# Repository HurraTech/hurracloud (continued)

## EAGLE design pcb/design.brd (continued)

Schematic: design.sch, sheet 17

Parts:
C16, C18, C22, C23, C24, C26, C27, C28, C29, C31, C32, C33, C294, C295, C296, C303, C314: GRM033R60J104KE19D; 0201
C17, C25, C34: CGB3B1X5R1A475K055AC; 0603
C19: 22uF; 0805
C20, C21: GRM0335C1H220JA01D; 0201
IC7: EP5368QI; EP-3X3MMQFN16
R3, R65, R69: RC0201JR-070RL; 0201
R9, R67: DNP; 0201
R10, R11: ERJ-1GEJ204C; 0201
R13: 1M0; 0201
R14, R15: RC0201FR-0710KL; 0201
R16: ERJ-1GEF1202C; 0201
R66: ERJ-1GNF10R0C; 0201
U15: USB5744/2G; VQFN56
Y2: ABM7-25.000MHZ-D2Y-T; CS10

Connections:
14.3.3V_VCC_3.3: C16.1, C17.1, C22.1, C23.1, C24.1, C25.1, IC7.10 (VS2), IC7.12 (VS0), IC7.13 (ENABLE), IC7.14 (VIN), R9.2, R14.2, R15.2, R67.2, U15.16 (VDD33), U15.31 (VDD33), U15.44 (VDD33), U15.55 (VDD33); also elsewhere on the board
16.USBH1_D_N: U15.46 (USB2UP_DM); also elsewhere on the board
16.USBH1_D_P: U15.45 (USB2UP_DP); also elsewhere on the board
16.USBH1_SSRX_N: C295.1; also elsewhere on the board
16.USBH1_SSRX_P: C296.1; also elsewhere on the board
16.USBH1_SSTX_N: C303.1; also elsewhere on the board
16.USBH1_SSTX_P: C294.1; also elsewhere on the board
19.USBH1_DRV_VBUS: R65.2; also elsewhere on the board
19.USBH1_D_N: U15.2 (USB2DN_DM1); also elsewhere on the board
19.USBH1_D_P: U15.1 (USB2DN_DP1); also elsewhere on the board
19.USBH1_NOC: R65.1, U15.36 (PRT_CTL1); also elsewhere on the board
19.USBH1_SSRX_N: U15.7 (USB3DN_RXDM1); also elsewhere on the board
19.USBH1_SSRX_P: U15.6 (USB3DN_RXDP1); also elsewhere on the board
19.USBH1_SSTX_N: U15.4 (USB3DN_TXDM1); also elsewhere on the board
19.USBH1_SSTX_P: U15.3 (USB3DN_TXDP1); also elsewhere on the board
19.USBH2_DRV_VBUS: R69.2; also elsewhere on the board
19.USBH2_D_N: U15.9 (USB2DN_DM2); also elsewhere on the board
19.USBH2_D_P: U15.8 (USB2DN_DP2); also elsewhere on the board
19.USBH2_NOC: R69.1, U15.35 (PRT_CTL2); also elsewhere on the board
19.USBH2_SSRX_N: U15.14 (USB3DN_RXDM2); also elsewhere on the board
19.USBH2_SSRX_P: U15.13 (USB3DN_RXDP2); also elsewhere on the board
19.USBH2_SSTX_N: U15.11 (USB3DN_TXDM2); also elsewhere on the board
19.USBH2_SSTX_P: U15.10 (USB3DN_TXDP2); also elsewhere on the board
19.USBH3_DRV_VBUS: R3.2; also elsewhere on the board
19.USBH3_D_N: U15.18 (USB2DN_DM3); also elsewhere on the board
19.USBH3_D_P: U15.17 (USB2DN_DP3); also elsewhere on the board
19.USBH3_NOC: R3.1, U15.34 (PRT_CTL3); also elsewhere on the board
19.USBH3_SSRX_N: U15.23 (USB3DN_RXDM3); also elsewhere on the board
19.USBH3_SSRX_P: U15.22 (USB3DN_RXDP3); also elsewhere on the board
19.USBH3_SSTX_N: U15.20 (USB3DN_TXDM3); also elsewhere on the board
19.USBH3_SSTX_P: U15.19 (USB3DN_TXDP3); also elsewhere on the board
CAP_RXD_N$19: C295.2, U15.48 (USB3UP_TXDM)
CAP_RXD_P$19: C296.2, U15.47 (USB3UP_TXDP)
CAP_TXD_N$19: C303.2, U15.51 (USB3UP_RXDM)
CAP_TXD_P$19: C294.2, U15.50 (USB3UP_RXDP)
CFG_BC_EN$19: R11.2, R67.1, U15.40 (SPI_DI)
CFG_NON_REM$19: R9.1, R10.2, U15.41 (SPI_CE_N)
GND: C16.2, C17.2, C18.2, C19.2, C20.2, C21.2, C22.2, C23.2, C24.2, C25.2, C26.2, C27.2, C28.2, C29.2, C31.2, C32.2, C33.2, C34.2, C314.2, IC7.2 (PGND), IC7.6 (AGND), IC7.11 (VS1), R10.1, R11.1, R16.1, U15.52 (ATEST), U15.P$1 (VSS), U15.P$2 (VSS), U15.P$3 (VSS), U15.P$4 (VSS), U15.P$5 (VSS), U15.P$6 (VSS), U15.P$7 (VSS), U15.P$8 (VSS), U15.P$9 (VSS), U15.P$10 (VSS), U15.P$11 (VSS), U15.P$12 (VSS), U15.P$13 (VSS), U15.P$14 (VSS), U15.P$15 (VSS), U15.P$16 (VSS), U15.P$17 (VSS), U15.P$18 (VSS), U15.P$19 (VSS), U15.P$20 (VSS), U15.P$21 (VSS), U15.P$22 (VSS), U15.P$23 (VSS), U15.P$24 (VSS), U15.P$25 (VSS); also elsewhere on the board
RBIAS$19: R16.2, U15.56 (RBIAS)
RESET_N$19: R14.1, U15.42 (RESET_N)
USBH4_PCTL$19: U15.32 (PRT_CTL4)
VBUS_DET$19: R15.1, U15.37 (VBUS_DET)
VCC_1.2$19: C18.1, C19.1, C26.1, C27.1, C28.1, C29.1, C31.1, C32.1, C33.1, C34.1, C314.1, IC7.5 (VSENSE), IC7.7 (VOUT), IC7.8 (VOUT), U15.5 (VDD12), U15.12 (VDD12), U15.15 (VDD12), U15.21 (VDD12), U15.28 (VDD12), U15.33 (VDD12), U15.43 (VDD12), U15.49 (VDD12)
XTALIN$19: C21.1, R13.2, U15.54 (XTALIN), Y2.2
XTALOUT2$19: C20.1, R66.1, Y2.1
XTALOUT$19: R13.1, R66.2, U15.53 (XTALOUT)

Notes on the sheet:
4-Port USB 3.0 Hub

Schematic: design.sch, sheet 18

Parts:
C3: C1608X5R1A106M080AC; 0603
C7, C306: GRM31CR60J227ME11L; 1206
C8, C9, C10, C11, C304: GRM033R60J104KE19D; 0201
C305: GRM033R61C103KA12D; 0201
FB4, FB15, FB16, FB17: BLM15PX121SN1D; 0402
J6: GSB311231HR; USB3-A-H-DUAL
L4, L5, L6, L16, L17, L18: DLP11SN900HL2L; 0504-DLP11S
U2, U5, U6, U7, U20, U21: TPD4E02B04DQAR; UFDFN-10
U24: TPS2066CDGNR; MSOP8-PAD

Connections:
19.USBH1_DRV_VBUS: U24.3 (EN1); also elsewhere on the board
19.USBH1_D_N: L18.2; also elsewhere on the board
19.USBH1_D_P: L18.3; also elsewhere on the board
19.USBH1_GND_DRAIN: J6.7 (GND_DRAIN1), U7.2, U7.9 (P2)
19.USBH1_NOC: U24.8 (NOC1); also elsewhere on the board
19.USBH1_SSRX_N: L16.3; also elsewhere on the board
19.USBH1_SSRX_P: L16.2; also elsewhere on the board
19.USBH1_SSTX_N: C9.1; also elsewhere on the board
19.USBH1_SSTX_P: C8.1; also elsewhere on the board
19.USBH1_VBUS: FB4.2, U24.7 (OUT1)
19.USBH2_DRV_VBUS: U24.4 (EN2); also elsewhere on the board
19.USBH2_D_N: L4.2; also elsewhere on the board
19.USBH2_D_P: L4.3; also elsewhere on the board
19.USBH2_GND_DRAIN: J6.16 (GND_DRAIN2), U2.4 (P3), U2.7 (P3)
19.USBH2_NOC: U24.5 (NOC2); also elsewhere on the board
19.USBH2_SSRX_N: L5.3; also elsewhere on the board
19.USBH2_SSRX_P: L5.2; also elsewhere on the board
19.USBH2_SSTX_N: C11.1; also elsewhere on the board
19.USBH2_SSTX_P: C10.1; also elsewhere on the board
19.USBH2_VBUS: FB17.2, U24.6 (OUT2)
24.5.0V_VCC_5.0: C304.1, FB16.1; also elsewhere on the board
A_GNDF$20: C305.1, FB15.2, J6.4 (GND1), J6.13 (GND2), U5.1, U5.10 (P1), U21.1, U21.10 (P1)
A_USB_D_N$20: J6.2 (D1-), L18.1, U7.1, U7.10 (P1)
A_USB_D_P$20: J6.3 (D1+), L18.4, U7.5 (P4), U7.6 (P4)
A_VBUS_$20: C306.1, FB4.1, J6.1 (VBUS1), U6.1, U6.10 (P1)
B_USB_D_N$20: J6.11 (D2-), L4.1, U2.5 (P4), U2.6 (P4)
B_USB_D_P$20: J6.12 (D2+), L4.4, U2.1, U2.10 (P1)
B_VBUS_$20: C7.1, FB17.1, J6.10 (VBUS2), U20.5 (P4), U20.6 (P4)
CAP_A_TX_N$20: C9.2, L17.3
CAP_A_TX_P$20: C8.2, L17.2
CAP_B_TX_N$20: C11.2, L6.3
CAP_B_TX_P$20: C10.2, L6.2
COMMON_SHIELD: J6.S1 (SH1), J6.S2 (SH2), J6.S3 (SH3), J6.S4 (SH4), U2.3 (SHIELD), U2.8 (SHIELD), U5.3 (SHIELD), U5.8 (SHIELD), U6.3 (SHIELD), U6.8 (SHIELD), U7.3 (SHIELD), U7.8 (SHIELD), U20.3 (SHIELD), U20.8 (SHIELD), U21.3 (SHIELD), U21.8 (SHIELD); also elsewhere on the board
GND: C3.2, C7.2, C304.2, C305.2, C306.2, FB15.1, U24.1 (GND), U24.TP (GND); also elsewhere on the board
SSRX1_N$20: J6.5 (SSRX1-), L16.4, U5.4 (P3), U5.7 (P3)
SSRX1_P$20: J6.6 (SSRX1+), L16.1, U5.5 (P4), U5.6 (P4)
SSRX2_N$20: J6.14 (SSRX2-), L5.4, U21.4 (P3), U21.7 (P3)
SSRX2_P$20: J6.15 (SSRX2+), L5.1, U21.5 (P4), U21.6 (P4)
SSTX1_N$20: J6.8 (SSTX1-), L17.4, U6.5 (P4), U6.6 (P4)
SSTX1_P$20: J6.9 (SSTX1+), L17.1, U6.4 (P3), U6.7 (P3)
SSTX2_N$20: J6.17 (SSTX2-), L6.4, U20.1, U20.10 (P1)
SSTX2_P$20: J6.18 (SSTX2+), L6.1, U20.2, U20.9 (P2)
VBUSF$20: C3.1, FB16.2, U24.2 (IN)

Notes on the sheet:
USB 3.0 Stacking Dual

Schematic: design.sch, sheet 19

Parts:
J7: 70553-0002; 1X03_90_TH_SHROUD

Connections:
21.5.5-16V_VCC_BATT: J7.3; also elsewhere on the board
FRAME$21: J7.1
GND: J7.2; also elsewhere on the board

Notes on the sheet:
Molex 70553 3-Pin Header (Power Provides)

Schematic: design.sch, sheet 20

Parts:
C308, C309, C311, C312: GRM033R60J104KE19D; 0201
C310: GRM31CR60J227ME11L; 1206
D16: PS04LTVA1; D0402
FB18, FB19, FB20: BLM15PX121SN1D; 0402
IC9: SN74LV1T126DCKR; SC70-5
IC10: TPS2065CDGNR; MSOP8-PAD
J8: 10117836-002LF; USB3-A-H-VERT
L19, L20, L21: DLP11SN900HL2L; 0504-DLP11S
U22, U23: TPD4E02B04DQAR; UFDFN-10

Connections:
14.3.3V_VCC_3.3: C308.1, IC9.1 (OE), IC9.5 (VCC); also elsewhere on the board
16.USBH2_DRV_VBUS: IC9.2 (I); also elsewhere on the board
16.USBH2_D_N: L19.2; also elsewhere on the board
16.USBH2_D_P: L19.3; also elsewhere on the board
16.USBH2_GND_DRAIN: D16.P2, FB20.2, J8.DRAIN (GND_DRAIN), U23.4 (P3), U23.7 (P3)
16.USBH2_NOC: IC10.5 (NOC); also elsewhere on the board
16.USBH2_SSRX_N: L20.3; also elsewhere on the board
16.USBH2_SSRX_P: L20.2; also elsewhere on the board
16.USBH2_SSTX_N: C311.1; also elsewhere on the board
16.USBH2_SSTX_P: C312.1; also elsewhere on the board
16.USBH2_VBUS: FB18.1, IC10.6 (OUT), IC10.7 (OUT), IC10.8 (OUT)
24.5.0V_VCC_5.0: C309.1, IC10.2 (IN), IC10.3 (IN); also elsewhere on the board
COMMON_SHIELD: D16.P1, J8.SH1, J8.SH2, U22.3 (SHIELD), U22.8 (SHIELD), U23.3 (SHIELD), U23.8 (SHIELD); also elsewhere on the board
GND: C308.2, C309.2, C310.2, FB19.1, FB20.1, IC9.3 (GND), IC10.1 (GND), IC10.TP (GND); also elsewhere on the board
USBH_CPEN_3V$22: IC9.4 (O), IC10.4 (EN)
USBH_D_N$22: J8.D-, L19.1, U22.1, U22.10 (P1)
USBH_D_P$22: J8.D+, L19.4, U23.5 (P4), U23.6 (P4)
USBH_GND$22: FB19.2, J8.GND
USBH_VBUSF$22: C310.1, FB18.2, J8.VBUS, U22.2, U22.9 (P2)
USB_CAP_SSTX_N$22: C311.2, L21.3
USB_CAP_SSTX_P$22: C312.2, L21.2
USB_SSRX_N$22: J8.SSRX-, L20.4, U23.1, U23.10 (P1)
USB_SSRX_P$22: J8.SSRX+, L20.1, U23.2, U23.9 (P2)
USB_SSTX_N$22: J8.SSTX-, L21.4, U22.4 (P3), U22.7 (P3)
USB_SSTX_P$22: J8.SSTX+, L21.1, U22.5 (P4), U22.6 (P4)

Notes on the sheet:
USB 3.0 HOST (Vertical)

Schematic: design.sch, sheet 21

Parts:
C2: GRM31CR60J227ME11L; 1206
C4, C5, C6, C318: GRM033R60J104KE19D; 0201
D17: PS04LTVA1; D0402
FB1, FB2, FB3: BLM15PX121SN1D; 0402
IC1: TPS2065CDGNR; MSOP8-PAD
IC2: SN74LV1T126DCKR; SC70-5
J1: 10117836-002LF; USB3-A-H-VERT
L1, L3, L22: DLP11SN900HL2L; 0504-DLP11S
U3, U4: TPD4E02B04DQAR; UFDFN-10

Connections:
14.3.3V_VCC_3.3: C4.1, IC2.1 (OE), IC2.5 (VCC); also elsewhere on the board
19.USBH3_DRV_VBUS: IC2.2 (I); also elsewhere on the board
19.USBH3_D_N: L1.2; also elsewhere on the board
19.USBH3_D_P: L1.3; also elsewhere on the board
19.USBH3_GND_DRAIN: D17.P2, FB3.2, J1.DRAIN (GND_DRAIN), U4.4 (P3), U4.7 (P3)
19.USBH3_NOC: IC1.5 (NOC); also elsewhere on the board
19.USBH3_SSRX_N: L22.3; also elsewhere on the board
19.USBH3_SSRX_P: L22.2; also elsewhere on the board
19.USBH3_SSTX_N: C5.1; also elsewhere on the board
19.USBH3_SSTX_P: C6.1; also elsewhere on the board
19.USBH3_VBUS: FB1.1, IC1.6 (OUT), IC1.7 (OUT), IC1.8 (OUT)
24.5.0V_VCC_5.0: C318.1, IC1.2 (IN), IC1.3 (IN); also elsewhere on the board
COMMON_SHIELD: D17.P1, J1.SH1, J1.SH2, U3.3 (SHIELD), U3.8 (SHIELD), U4.3 (SHIELD), U4.8 (SHIELD); also elsewhere on the board
GND: C2.2, C4.2, C318.2, FB2.1, FB3.1, IC1.1 (GND), IC1.TP (GND), IC2.3 (GND); also elsewhere on the board
USBH_CPEN_3V$23: IC1.4 (EN), IC2.4 (O)
USBH_D_N$23: J1.D-, L1.1, U3.1, U3.10 (P1)
USBH_D_P$23: J1.D+, L1.4, U4.5 (P4), U4.6 (P4)
USBH_GND$23: FB2.2, J1.GND
USBH_VBUSF$23: C2.1, FB1.2, J1.VBUS, U3.2, U3.9 (P2)
USB_CAP_SSTX_N$23: C5.2, L3.3
USB_CAP_SSTX_P$23: C6.2, L3.2
USB_SSRX_N$23: J1.SSRX-, L22.4, U4.1, U4.10 (P1)
USB_SSRX_P$23: J1.SSRX+, L22.1, U4.2, U4.9 (P2)
USB_SSTX_N$23: J1.SSTX-, L3.4, U3.4 (P3), U3.7 (P3)
USB_SSTX_P$23: J1.SSTX+, L3.1, U3.5 (P4), U3.6 (P4)

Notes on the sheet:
USB 3.0 HOST (Vertical)

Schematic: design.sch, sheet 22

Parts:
C13: CL31A106KBHNNNE; 1206
C30: C0603C103K5RACTU; 0603
C52, C78: GRM033R61C103KA12D; 0201
C79: EEE-1EA331UP; PANASONIC_F
D18: CDBC540-G; DO-214AB
L2: IHLP3232DZER100M11; 3232DZ
R12: RC0201FR-07100KL; 0201
R17: ERJ-2RKF3162X; 0402
R68: CR0805-J/-000ELF; 0805
TP1: DNP; TP0500
U1: TPS5450QDDARQ1; 8SO_POWERPAD

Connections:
21.5.5-16V_VCC_BATT: R68.1, TP1.1; also elsewhere on the board
24.5.0V_VCC_5.0: C78.1, C79.+ (1), L2.2, R12.1; also elsewhere on the board
BOOT$24: C52.1, U1.1 (BOOT)
GND: C13.2, C30.2, C78.2, C79.- (2), D18.A, R17.2, U1.6 (GND1), U1.9 (GND2), U1.PWRPAD1 (GND2), U1.PWRPAD2 (GND2), U1.PWRPAD3 (GND2), U1.PWRPAD4 (GND2), U1.PWRPAD5 (GND2), U1.PWRPAD6 (GND2), U1.PWRPAD7 (GND2), U1.PWRPAD8 (GND2); also elsewhere on the board
PH$24: C52.2, D18.C, L2.1, U1.8 (PH)
VSENSE$24: R12.2, R17.1, U1.4 (VSENSE)
V_POWER$24: C13.1, C30.1, R68.2, U1.7 (VIN)

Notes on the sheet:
5V/5A Regulator

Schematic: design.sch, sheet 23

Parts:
C319: GRM0335C1E470JA01D; 0201
D19: B72590D0050A060; D0402
R70: RC0201FR-0710KL; 0201
R71: ERJ-1GNJ151C; 0201
S2: EVQ-P7C01P; EVQP-4

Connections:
14.VLOGIC_VLOGIC: R70.2; also elsewhere on the board
14.nRESET_NRESET: C319.1, R71.2; also elsewhere on the board
BTN_A$25: D19.P2, R70.1, R71.1, S2.B@2 (B')
GND: C319.2, D19.P1, S2.A@1 (A); also elsewhere on the board

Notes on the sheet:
Pushbutton R/A

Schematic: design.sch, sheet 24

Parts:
C1: GRM0335C1E470JA01D; 0201
D1: B72590D0050A060; D0402
R1: RC0201FR-0710KL; 0201
R2: ERJ-1GNJ151C; 0201
S1: EVQ-PLDA15; EVQ

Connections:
14.USB3_CC1_GPIO: C1.1, R2.2; also elsewhere on the board
14.VLOGIC_VLOGIC: R1.2; also elsewhere on the board
BTN_A$26: D1.P2, R1.1, R2.1, S1.B@2 (B')
GND: C1.2, D1.P1, S1.A@1 (A); also elsewhere on the board

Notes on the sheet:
Pushbutton

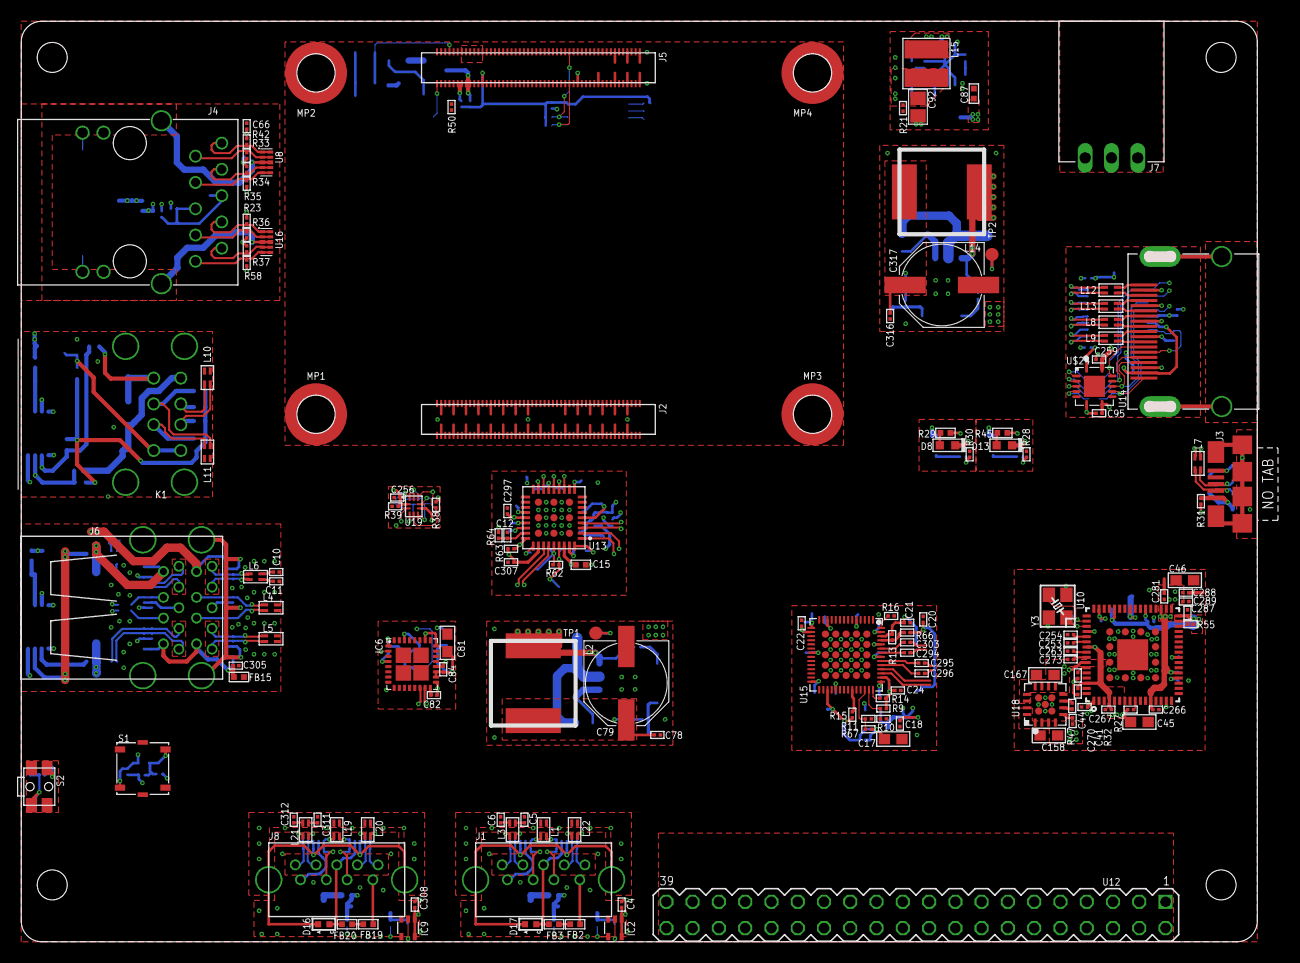
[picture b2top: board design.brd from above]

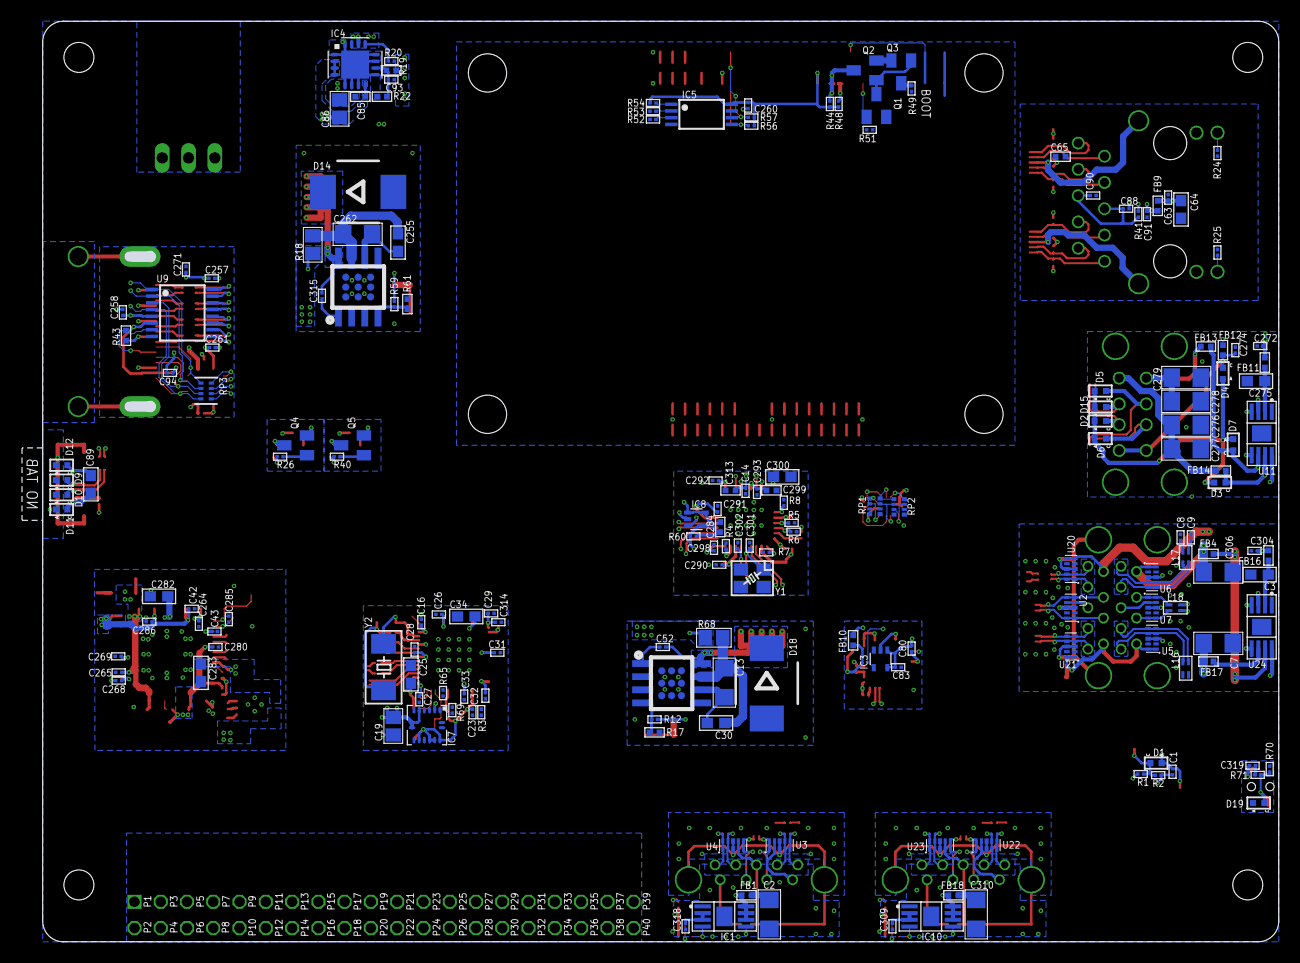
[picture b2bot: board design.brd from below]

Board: 6 copper layers, 121.5 x 89.0 mm, 326 parts (177 on the bottom side), 273 nets.

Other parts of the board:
U$11, U$13, U$17, U$28: DNP; GEPPETTO_HOLE_2.9

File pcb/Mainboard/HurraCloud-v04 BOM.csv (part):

Reference Designator,Description,Manufacturer,Manufacturer Part Number,Suppliers,Package,Quantity,Custom Library Id,Conn 1 Type,Conn 0 Type,Value,Height,Dm,Dx,Dy,Sheetno,Dr,Footprint Variant Name 13,Footprint Variant Name 12,Footprint Variant Name 11,Footprint Variant Name 10,Footprint Variant Name 17,Footprint Variant Name 16,Footprint Variant Name 15,Footprint Variant Name 14,Footprint Variant Name 9,Footprint Variant Name 8,Footprint Variant Name 7,Footprint Variant Name 6,Footprint Variant Name 5,Footprint Variant Name 4,Footprint Variant Name 3,Footprint Variant Name 2,Footprint Variant Name 1,Footprint Variant Name 0,Footprint Variant Name 18,Conn 7 Type,Conn 3 Type,Conn 4 Type,Conn 5 Type,Conn 8 Type,Conn 6 Type,Conn 2 Type,Conn 10 Type,Conn 11 Type,Conn 16 Type,Conn 13 Type,Conn 15 Type,Conn 12 Type,Conn 9 Type,Conn 14 Type,Conn 22 Type,Conn 19 Type,Conn 17 Type,Conn 20 Type,Conn 18 Type,Conn 25 Type,Mpn,Conn 21 Type,Oc Farnell,Oc Newark,Conn 24 Type,Conn 23 Type,Conn 76 Type,Conn 34 Type,Conn 67 Type,Conn 54 Type,Conn 51 Type,Conn 28 Type,Conn 88 Type,Conn 40 Type,Conn 78 Type,Conn 81 Type,Conn 73 Type,Conn 39 Type,Conn 42 Type,Conn 80 Type,Conn 93 Type,Conn 43 Type,Conn 46 Type,Conn 91 Type,Conn 48 Type,Conn 58 Type,Conn 95 Type,Conn 41 Type,Conn 53 Type,Conn 77 Type,Conn 96 Type,Conn 83 Type,Conn 38 Type,Conn 70 Type,Digi-Key Purchase Url,Conn 86 Type,Conn 75 Type,Mf,Conn 44 Type,Conn 64 Type,Mp,Conn 89 Type,Conn 84 Type,Conn 68 Type,Conn 36 Type,Conn 82 Type,Conn 62 Type,Conn 66 Type,Conn 72 Type,Conn 79 Type,Conn 55 Type,Conn 47 Type,Conn 26 Type,Conn 87 Type,Conn 60 Type,Conn 94 Type,Conn 61 Type,Conn 56 Type,Conn 65 Type,Conn 27 Type,Conn 99 Type,Conn 90 Type,Conn 49 Type,Conn 69 Type,Description,Conn 71 Type,Conn 37 Type,Digi-Key Part Number,Conn 52 Type,Conn 31 Type,Conn 59 Type,Conn 74 Type,Conn 50 Type,Conn 30 Type,Conn 35 Type,Conn 29 Type,Conn 33 Type,Conn 92 Type,Conn 63 Type,Conn 97 Type,Conn 98 Type,Conn 85 Type,Conn 32 Type,Conn 57 Type,Conn 45 Type
C1,,,GRM0335C1E470JA01D,,,1,qualified_1,passive,passive,GRM0335C1E470JA01D,0.25,,,,,,,,,,,,,,,,,,,,,,,,,,,,,,,,,,,,,,,,,,,,,,,,,,,,,,,,,,,,,,,,,,,,,,,,,,,,,,,,,,,,,,,,,,,,,,,,,,,,,,,,,,,,,,,,,,,,,,,,,,,,,,,,,,
C10 C11 C8 C9,,,GRM033R60J104KE19D,,,4,qualified_1@eagle_src_repo_d00aa7e5b0aed880e2479218df7f64b10b504166,passive,passive,GRM033R60J104KE19D,0.25,,,,,,,,,,,,,,,,,,,,,,,,,,,,,,,,,,,,,,,,,,,,,,,,,,,,,,,,,,,,,,,,,,,,,,,,,,,,,,,,,,,,,,,,,,,,,,,,,,,,,,,,,,,,,,,,,,,,,,,,,,,,,,,,,,
C12 C14 C290 C291 C292 C293 C297 C298 C307,,,GRM033R60J104KE19D,,,9,qualified_1,passive,passive,GRM033R60J104KE19D,0.25,0,5.600,28.400,2,90.000,,,,,,,,,,,,,,,,,,,,,,,,,,,,,,,,,,,,,,,,,,,,,,,,,,,,,,,,,,,,,,,,,,,,,,,,,,,,,,,,,,,,,,,,,,,,,,,,,,,,,,,,,,,,,,,,,,,,,,,,,,,,,
C13 C262,,,CL31A106KBHNNNE,,,2,qualified_1@eagle_src_repo_f26ba765df9be4aea4dc36b2b99244de1327d3cb,passive,passive,CL31A106KBHNNNE,0.51,,,,,,,,,,,,,,,,,,,,,,,,,,,,,,,,,,,,,,,,,,,,,,,,,,,,,,,,,,,,,,,,,,,,,,,,,,,,,,,,,,,,,,,,,,,,,,,,,,,,,,,,,,,,,,,,,,,,,,,,,,,,,,,,,,
C15 C299 C313,,,CL05A105KO5NNNC,,,3,qualified_1,passive,passive,CL05A105KO5NNNC,0.35,,,,,,,,,,,,,,,,,,,,,,,,,,,,,,,,,,,,,,,,,,,,,,,,,,,,,,,,,,,,,,,,,,,,,,,,,,,,,,,,,,,,,,,,,,,,,,,,,,,,,,,,,,,,,,,,,,,,,,,,,,,,,,,,,,
C158 C167,,,CGB3B1X5R1A475K055AC,,,2,qualified_1@eagle_src_repo_701dee95a4f0c9d27f896634bd535ea9ef5a137e,passive,passive,CGB3B1X5R1A475K055AC,0.5,,,,,,,,,,,,,,,,,,,,,,,,,,,,,,,,,,,,,,,,,,,,,,,,,,,,,,,,,,,,,,,,,,,,,,,,,,,,,,,,,,,,,,,,,,,,,,,,,,,,,,,,,,,,,,,,,,,,,,,,,,,,,,,,,,
C16 C18 C22 C23 C24 C26 C27 C28 C29 C294 C295 C296 C303 C31 C314 C32 C33,,,GRM033R60J104KE19D,,,17,qualified_1@eagle_src_repo_b39d46a5feff4f7ade7f2a4f70c4d4847a03ea32,passive,passive,GRM033R60J104KE19D,0.25,,,,,,,,,,,,,,,,,,,,,,,,,,,,,,,,,,,,,,,,,,,,,,,,,,,,,,,,,,,,,,,,,,,,,,,,,,,,,,,,,,,,,,,,,,,,,,,,,,,,,,,,,,,,,,,,,,,,,,,,,,,,,,,,,,
C17,,,CGB3B1X5R1A475K055AC,,,1,qualified_1@eagle_src_repo_b39d46a5feff4f7ade7f2a4f70c4d4847a03ea32,passive,passive,CGB3B1X5R1A475K055AC,0.5,0,70.250,17.350,5,180.000,,,,,,,,,,,,,,,,,,,,,,,,,,,,,,,,,,,,,,,,,,,,,,,,,,,,,,,,,,,,,,,,,,,,,,,,,,,,,,,,,,,,,,,,,,,,,,,,,,,,,,,,,,,,,,,,,,,,,,,,,,,,,
C19,,,C,,,1,qualified_1@eagle_src_repo_b39d46a5feff4f7ade7f2a4f70c4d4847a03ea32,passive,passive,22uF,0.25,,,,,,R1000UF63V,R1000UF,R10UF,R100UF,1UF-FILM-250V,CA1000UF-50V,PANASONIC_C,CPOL-D,PANASONIC_D,PANASONIC_F,0201,BZ05,BZ02,1206,0805,0603,0402,1210,,,,,,,,,,,,,,,,,,,,,,,,,,,,,,,,,,,,,,,,,,,,,,,,,,,,,,,,,,,,,,,,,,,,,,,,,,,,,,,,,,,,,,,,,,,,,,,,,,,,,,,,,,,
C2 C310,,,GRM31CR60J227ME11L,,,2,qualified_1@eagle_src_repo_0b5741b5d4abbb92614c593c71c49b300549e5ff,passive,passive,GRM31CR60J227ME11L,0.51,0,13.200,27.200,2,90.000,,,,,,,,,,,,,,,,,,,,,,,,,,,,,,,,,,,,,,,,,,,,,,,,,,,,,,,,,,,,,,,,,,,,,,,,,,,,,,,,,,,,,,,,,,,,,,,,,,,,,,,,,,,,,,,,,,,,,,,,,,,,,
C20,,,GRM0335C1H220JA01D,,,1,qualified_1@eagle_src_repo_b39d46a5feff4f7ade7f2a4f70c4d4847a03ea32,passive,passive,GRM0335C1H220JA01D,0.25,0,-17.200,6.600,9,-270.000,,,,,,,,,,,,,,,,,,,,,,,,,,,,,,,,,,,,,,,,,,,,,,,,,,,,,,,,,,,,,,,,,,,,,,,,,,,,,,,,,,,,,,,,,,,,,,,,,,,,,,,,,,,,,,,,,,,,,,,,,,,,,
C21,,,GRM0335C1H220JA01D,,,1,qualified_1@eagle_src_repo_b39d46a5feff4f7ade7f2a4f70c4d4847a03ea32,passive,passive,GRM0335C1H220JA01D,0.25,0,-20.800,6.600,9,-90.000,,,,,,,,,,,,,,,,,,,,,,,,,,,,,,,,,,,,,,,,,,,,,,,,,,,,,,,,,,,,,,,,,,,,,,,,,,,,,,,,,,,,,,,,,,,,,,,,,,,,,,,,,,,,,,,,,,,,,,,,,,,,,
C25 C34,,,CGB3B1X5R1A475K055AC,,,2,qualified_1@eagle_src_repo_b39d46a5feff4f7ade7f2a4f70c4d4847a03ea32,passive,passive,CGB3B1X5R1A475K055AC,0.5,,,,,,,,,,,,,,,,,,,,,,,,,,,,,,,,,,,,,,,,,,,,,,,,,,,,,,,,,,,,,,,,,,,,,,,,,,,,,,,,,,,,,,,,,,,,,,,,,,,,,,,,,,,,,,,,,,,,,,,,,,,,,,,,,,
C253 C254 C263 C264 C265 C266 C267 C268 C269 C273 C280 C281 C286 C287 C288 C289 C41 C42 C43 C44,,,GRM033R60J104KE19D,,,20,qualified_1@eagle_src_repo_701dee95a4f0c9d27f896634bd535ea9ef5a137e,passive,passive,GRM033R60J104KE19D,0.25,,,,,,,,,,,,,,,,,,,,,,,,,,,,,,,,,,,,,,,,,,,,,,,,,,,,,,,,,,,,,,,,,,,,,,,,,,,,,,,,,,,,,,,,,,,,,,,,,,,,,,,,,,,,,,,,,,,,,,,,,,,,,,,,,,
C255 C30,,,C0603C103K5RACTU,,,2,qualified_1@eagle_src_repo_f26ba765df9be4aea4dc36b2b99244de1327d3cb,passive,passive,C0603C103K5RACTU,0.5,,,,,,,,,,,,,,,,,,,,,,,,,,,,,,,,,,,,,,,,,,,,,,,,,,,,,,,,,,,,,,,,,,,,,,,,,,,,,,,,,,,,,,,,,,,,,,,,,,,,,,,,,,,,,,,,,,,,,,,,,,,,,,,,,,
C256,,,GRM033R60J104KE19D,,,1,qualified_1@eagle_src_repo_83354d0c2c11c8ce792d5cc032a7091e5ff73f00,passive,passive,GRM033R60J104KE19D,0.25,,,,,,,,,,,,,,,,,,,,,,,,,,,,,,,,,,,,,,,,,,,,,,,,,,,,,,,,,,,,,,,,,,,,,,,,,,,,,,,,,,,,,,,,,,,,,,,,,,,,,,,,,,,,,,,,,,,,,,,,,,,,,,,,,,
C257 C261,,,GRM033R61C103KA12D,,,2,qualified_1@eagle_src_repo_08f38ff5c3a3a6fa35c93a02bac883b74ea519d0,passive,passive,GRM033R61C103KA12D,0.25,0,30.550,33.500,6,0.000,,,,,,,,,,,,,,,,,,,,,,,,,,,,,,,,,,,,,,,,,,,,,,,,,,,,,,,,,,,,,,,,,,,,,,,,,,,,,,,,,,,,,,,,,,,,,,,,,,,,,,,,,,,,,,,,,,,,,,,,,,,,,
C258 C259 C95,,,GRM033R60J104KE19D,,,3,qualified_1@eagle_src_repo_08f38ff5c3a3a6fa35c93a02bac883b74ea519d0,passive,passive,GRM033R60J104KE19D,0.25,,,,,,,,,,,,,,,,,,,,,,,,,,,,,,,,,,,,,,,,,,,,,,,,,,,,,,,,,,,,,,,,,,,,,,,,,,,,,,,,,,,,,,,,,,,,,,,,,,,,,,,,,,,,,,,,,,,,,,,,,,,,,,,,,,
C260,,,GRM033R60J104KE19D,,,1,qualified_1@eagle_src_repo_23ecad3ae72028015427fba7d2ea5a80aee78817,passive,passive,GRM033R60J104KE19D,0.25,,,,,,,,,,,,,,,,,,,,,,,,,,,,,,,,,,,,,,,,,,,,,,,,,,,,,,,,,,,,,,,,,,,,,,,,,,,,,,,,,,,,,,,,,,,,,,,,,,,,,,,,,,,,,,,,,,,,,,,,,,,,,,,,,,
C270,,,GRM033R71A682KA01D,,,1,qualified_1@eagle_src_repo_701dee95a4f0c9d27f896634bd535ea9ef5a137e,passive,passive,GRM033R71A682KA01D,0.25,,,,,,,,,,,,,,,,,,,,,,,,,,,,,,,,,,,,,,,,,,,,,,,,,,,,,,,,,,,,,,,,,,,,,,,,,,,,,,,,,,,,,,,,,,,,,,,,,,,,,,,,,,,,,,,,,,,,,,,,,,,,,,,,,,
C271 C94,,,GRM033R60J104KE19D,,,2,qualified_1@eagle_src_repo_08f38ff5c3a3a6fa35c93a02bac883b74ea519d0,passive,passive,GRM033R60J104KE19D,0.25,0,30.550,33.500,6,0.000,,,,,,,,,,,,,,,,,,,,,,,,,,,,,,,,,,,,,,,,,,,,,,,,,,,,,,,,,,,,,,,,,,,,,,,,,,,,,,,,,,,,,,,,,,,,,,,,,,,,,,,,,,,,,,,,,,,,,,,,,,,,,
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
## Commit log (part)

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2020-08-17 rpi bug
2020-08-17 ocrssetting
2020-08-17 docker-compose for dav
2020-08-17 build and start scripts
2020-08-17 start script
2020-08-17 ES client changes
2020-08-17 script enhancements
2020-08-17 scripts
2020-08-17 aeshtetics
2020-08-17 debug message
2020-08-17 bug fix
2020-08-17 docker syncthing build
2020-08-18 multi-arch nginx-proxy
2020-08-18 progress bar fixes
2020-08-18 aesthetics
2020-08-18 build prod
2020-08-18 build enhancements
2020-08-18 fixed api hostname
2020-08-18 bug fixes
2020-08-18 index data in chart
2020-08-18 rails prod
2020-08-18 gdrive enhancements
2020-08-19 nginx-proxy arm
2020-08-19 nginx-proxy arm, yocto rpi64
2020-08-19 mounter bug fix
2020-08-19 yocto bug fix
2020-08-19 app runner fix
2020-08-19 too many update requests
2020-08-19 performance
2020-08-19 apprunner build
2020-08-19 hostname
2020-08-19 yocto dunfell
2020-08-19 yocto
2020-08-20 added virtualization to yocto
2020-08-20 enhancement
2020-08-20 always restart redis
2020-08-20 virtio in meta-rpi
2020-08-20 working yocto with docker
2020-08-20 remeoved virtio.scc / yocto
2020-08-20 docker-compose
2020-08-21 gcp cloudbuild
2020-08-21 multiarch cloudbuild
2020-08-21 cloudbuild mulitarch
2020-08-21 cicd
2020-08-22 bug fix in start script
2020-08-22 bug fixe
2020-08-22 cloudbuild nginx
2020-08-22 cloudbuild
2020-08-22 wpa fix
2020-08-22 swiched from yarn to npm
2020-08-22 cloudbuild bug fix
2020-08-22 multi-stage docker builds
2020-08-22 multi-stage docker builds fix
2020-08-22 switched apprunner to npm
2020-08-22 multi-stage docker builds fix & npm bug fixes
2020-08-22 logging
2020-08-22 build optimizations
2020-08-22 samaa npm/node upgrades
2020-08-22 build enhancemnts
2020-08-22 user node
2020-08-22 fixed apprunner builds
2020-08-22 build triggers scope
2020-08-22 fix perm
2020-08-22 multi-stage build apprunner
2020-08-22 fixed app-runner server with dummy app
2020-08-22 jawhar mounter fixes
2020-08-22 changed cloudbuild machine type
2020-08-22 deploy submodule
2020-08-22 cleanups, arch-agnostic
2020-08-22 hurrabuild access
2020-08-22 hurracloud systemd
2020-08-23 cleanups, u-boot, systemd
2020-08-23 mender
2020-08-23 fixed mender
2020-08-23 adjuted image size
2020-08-23 adjust size
2020-08-23 upload artifacts script
2020-08-23 hurrabuild scripts
2020-08-23 fixed script
2020-08-23 cleanups
2020-08-23 gitignore
2020-08-23 build scripts
2020-08-24 disabled mender
2020-08-24 switching to sysvinit
2020-08-24 enabling mender again
2020-08-24 working state
2020-08-25 bugfixes
2020-08-25 es oss
2020-08-25 started work on reducing image size
2020-08-25 using docker-compose/start from deploy submodule
2020-08-25 use /data for docker
2020-08-25 docker config in yocto
2020-08-25 reducing jawhar image size
2020-08-25 packaging /var/lib/docker.tar directly
2020-08-26 updated deploy submodule
2020-08-26 mulit-arch fixes
2020-08-26 multi arch
2020-08-26 jawhar es dependecies
2020-08-26 fixed hurracloud sevrice unit
2020-08-26 moved hurra-agent to separate repo
2020-08-26 added hurra-agent as submodule
2020-08-26 hurra-agent yocto
2020-08-26 mdns
2020-08-26 avahi fixes
2020-08-26 jawhar wait for es
2020-08-26 bugfix
2020-08-26 revert to standard cloudbuild instance size
2020-08-27 corrected paths
2020-08-27 changed app-store path
2020-08-27 moved app-store into jawhar image
2020-08-27 do not restart if stopped
2020-08-31 bug fixes, stable
2020-08-31 started work on elasticsearch
2020-08-31 elastcsearch WIP
2020-08-31 removed es container
2020-08-31 externalized es
2020-09-01 es logging
2020-09-01 es fixes
2020-09-01 redis
2020-09-01 externalized redis
2020-09-01 fix es check
2020-09-05 removed arch-dependant binary
2020-09-05 upgraded to ruby 2.7.
2020-09-05 upgraded bundler
2020-09-05 extract artifacts from docker images
2020-09-05 jawhar dockerfile fixes
2020-09-06 bundle without dev/prod in image
2020-09-06 install required share libs
2020-09-06 renamed hurra-agent to hurracloud-agent
2020-09-06 stable jawhar baked in yocto
2020-09-06 using nginx for samaa image
2020-09-06 removed byebug
2020-09-06 no more cors
2020-09-06 dev env
2020-09-06 cleanups, getting samaa to work on yocto
2020-09-07 auto db migrate on startup, moved es index settigns to fscrawler
2020-09-07 moutner no longer async
2020-09-07 reverted accidental change to samaa
2020-09-07 bug fix jawhar
2020-09-07 cleanup jawhar
2020-09-07 zahif systemd units, fixed samaa artifacts
2020-09-08 use /data partition
2020-09-08 setting JAVA_HOME
2020-09-12 go rewrite
2020-09-12 samaa refactors new backend
2020-09-14 integrating with jawhar
2020-09-15 search ux
2020-09-15 search using query string
2020-09-15 search / browse ux
2020-09-15 agent
2020-09-22 skip system partitoins
2020-09-24 new app store
2020-09-24 load image rpc
2020-09-25 app store
2020-09-25 functional openvpn!
2020-09-27 proxying applications webapps through jawhar
2020-09-30 switching to go-based apps
2020-09-30 clenaups
2020-09-30 dompose fix
2020-09-30 jawhar go recipe
2020-09-30 souq basic auth
2020-09-30 renamed agent to hagent
2020-09-30 nginx fix
2020-10-01 bleve search backend
2020-10-01 100% go
2020-10-01 removed meta-rust
2020-10-01 samaa fixes
2020-10-01 hagent fixes
2020-10-01 tmp dir for hagent, changed docker data dir
2020-10-01 internal storage
2020-10-01 internal storage path
2020-10-01 updated samaa
2020-10-02 updated jawhar and hagent
2020-10-02 updated jawhar
2020-10-02 update zahif
2020-10-02 update zahif, jawhar and samaa
2020-10-03 update jawhar and samaa
2020-10-04 updated submodules
2020-10-04 leveldb
2020-10-04 reduced paralaleism
2020-10-17 update jawhar, zahif and samaa
2020-10-18 unlimited uploda limit
2020-12-24 started working on case design
2020-12-24 corner brackets (wip)
2020-12-26 corner brackets completed
2020-12-26 finished front with hdd slots
2020-12-26 finished board holder
2020-12-26 case top
2020-12-26 re-did brackets
2020-12-26 fixed front panel (flipped)
2020-12-27 measurements
2020-12-27 case logo
2020-12-29 fixed missing right rail cut
2020-12-29 increased screw hole sizes
2020-12-29 re-did front panel slots
2020-12-29 rounded edges
2021-01-04 fixed screw holes
2021-01-05 testing two-part model
2021-01-06 more clearance for trays
2021-01-07 new separate variable for top cover screw holes
2021-01-07 increased inserts hole diameter
2021-01-07 good case state
2021-01-07 stl files
2021-01-08 reduced clearance spaces
2021-01-08 hdd tray front frame
2021-01-08 hdd front frame adjusments
2021-01-09 started working on sata plug holder
2021-01-10 fixed sata plug holder width
2021-01-10 fxied sketch attachment errors
2021-01-10 sata holder other side
2021-01-12 different approach for sata plug mount
2021-01-12 adapter mount
2021-01-12 no-slip sata plug mount
2021-01-14 no-slip wall on hdd tray
2021-01-14 adjusted sata plug mount locations
2021-01-14 adjusted hdd tray track dimension
2021-01-15 adjust top sata plug mount z
2021-01-21 corrected sata plug bracket length
2021-01-21 created separate part for hdd tray wall to avoid supports
2021-01-22 dimension adjustments
2021-01-24 adjusted HDD tray length (-1.5mm)
2021-01-24 removed extra padding around tray front
2021-01-25 adjusted sata plug mount dimensions; good state
2021-01-25 hdd no slip approach change
2021-01-25 shell changes, pcb
2021-01-26 pcb preliminary
2021-01-26 mounting hole for sata plug, adjusted tray dimensions
2021-01-27 README; updated submodules; cleaned up docker-compose
2021-01-27 plug mount hole location correction
2021-01-27 README formatting
2021-01-27 README.md edited online with Bitbucket
2021-01-28 thicker sata adapter
2021-01-28 README correction
2021-01-28 updated submodule commits
2021-01-28 git submodule update merge
2021-01-28 yocto vagrant environment
2021-01-28 thicker sata plug mount
2021-01-28 increased vagrant box disk size for yocto builds
2021-01-28 HDD tray handle
2021-01-28 flashing instructions
2021-01-29 start-all script, updated README, hagent submodule
2021-01-29 bash compatibility
2021-01-31 beveled case edges
2021-02-02 Initial import of mobile app
2021-02-02 Server type selection screen
2021-02-02 Pairing screen
2021-02-02 Deleted unused code
2021-02-02 Navigation
2021-02-02 Find computer card
2021-02-02 Services discovery
2021-02-02 thicker walls, more rounded edges
2021-02-03 Revert "thicker walls, more rounded edges"
    This reverts commit 63b503acc0d4a736eee6527bb935559427ccfd27.
2021-02-03 Complete onboarding + home screen routing
2021-02-03 Android fixes
2021-02-03 revert case changes
2021-02-03 updated start script to use air for hot reload + updated latest submodules
2021-02-03 updated souq submodule
2021-02-08 Home screen
2021-02-08 Build cloud + home screen list view
2021-02-08 UI Tweaks + Tab View
2021-02-09 Files tab + refactoring
2021-02-09 Refactoring + Souq view
2021-02-09 Add description to header widget
2021-02-09 Layout tweaks
2021-02-09 Refactored files to use generic list views
2021-02-09 Passing Image for more flexibility than String
2021-02-09 Settings screen + tweaks
2021-02-09 Pressable list items
2021-02-09 UI Tweaks
2021-02-09 Adjusted font size
2021-02-09 update submodules, fix start-all script for hagent
2021-02-10 Navigation for both iOS & Android
2021-02-10 Navigation from splash screen
2021-05-13 pcb specs
2021-05-13 update submodule
2021-05-14 update submoduels
2021-05-14 demo mode
2021-05-15 update submodules
2021-05-15 submodule update
2021-05-16 update submodule urls
2021-05-16 update repo url in instructions
2021-06-08 Create LICENSE
2021-06-09 cleanup
2021-06-27 started working on blockchain node
2021-08-04 fix keys initialization
2021-08-04 utilify functions for enc/dec
2021-09-28 fix meta-rpi submodule
2024-07-14 update setup steps
2024-07-14 typo
2024-07-14 clenaup hardware stuff
2024-07-14 clenaup more hardware stuff
2024-07-14 fix startup script
2024-07-14 track master branches
2024-07-14 rebase submodules
2024-07-14 updatd readme
2024-07-15 simplify os partition approach + bug fixes
2024-07-20 samaa upgrade
